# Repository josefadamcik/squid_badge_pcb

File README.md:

# squid_badge_pcb
SVG and KiCad files for a squid shaped pcb badge

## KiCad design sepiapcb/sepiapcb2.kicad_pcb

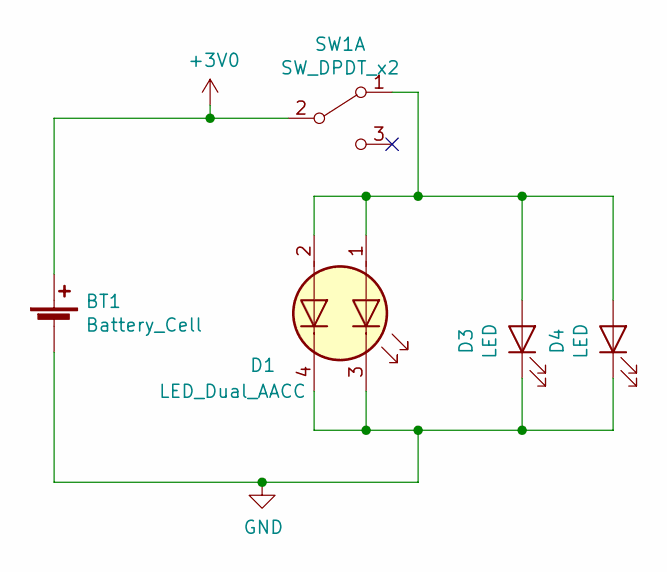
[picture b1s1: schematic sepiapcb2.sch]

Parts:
BT1: Battery_Cell; BatteryHolder_CR2032-BK-912xCR2032
D1: LED_Dual_AACC; sepia_footprint_enlarged_thttent_pcb
D3, D4: LED; LED_1206_3216Metric_ReverseMount_NoHole1.8x2.4mm
SW1: SW_DPDT_x2; SW_SPDT_PCM12

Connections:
+3V0: BT1.1 (+), SW1.2 (B)
GND: BT1.2 (-), D1.3 (K1), D1.4 (K2), D3.1 (K), D4.1 (K)
unnamed: D1.1 (A1), D1.2 (A2), D3.2 (A), D4.2 (A), SW1.1 (A)

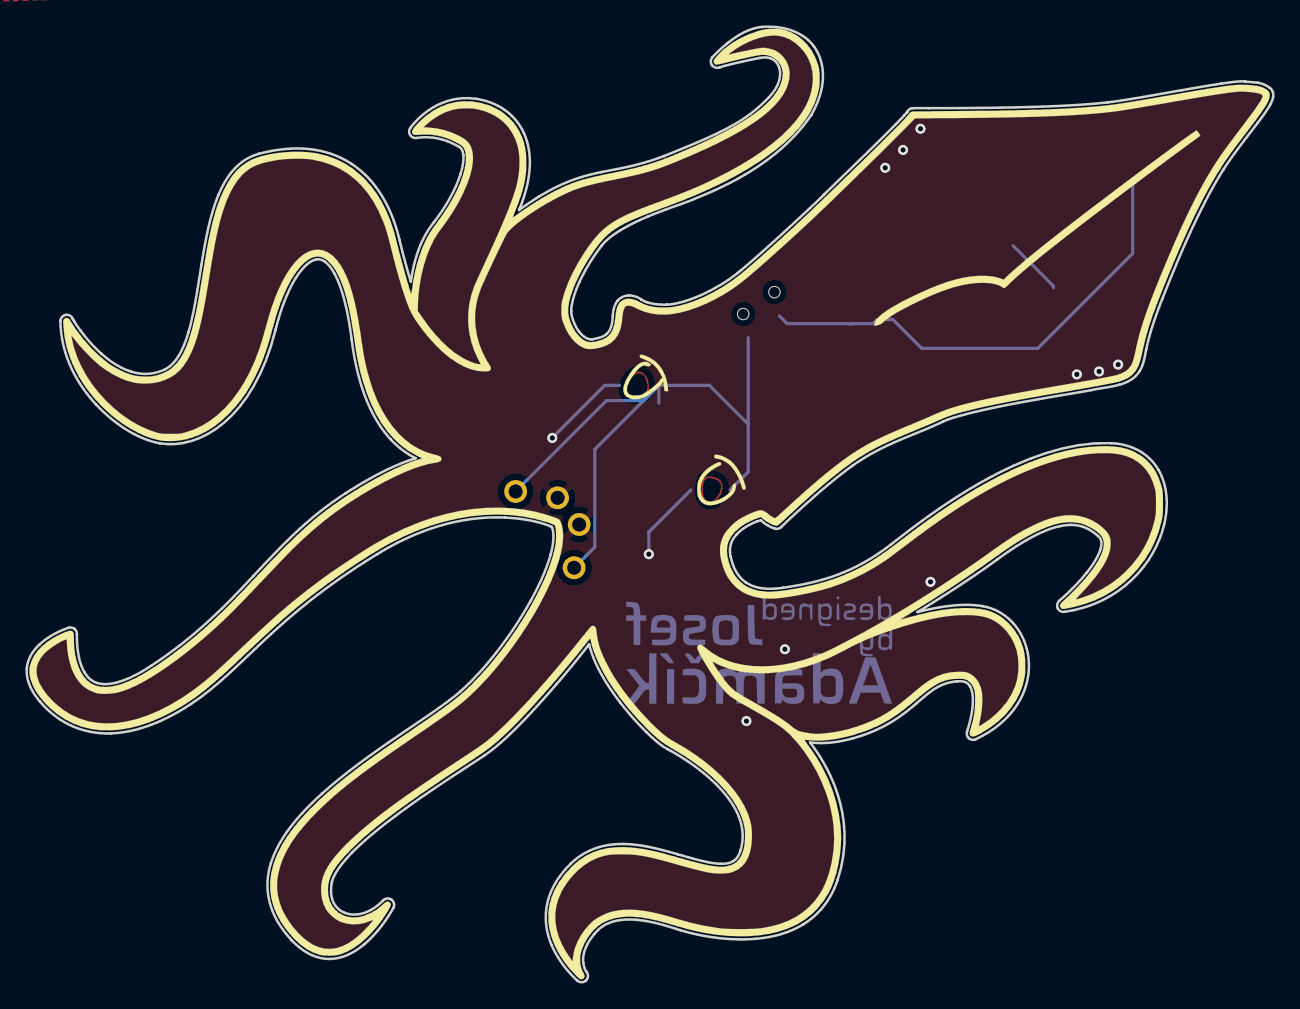
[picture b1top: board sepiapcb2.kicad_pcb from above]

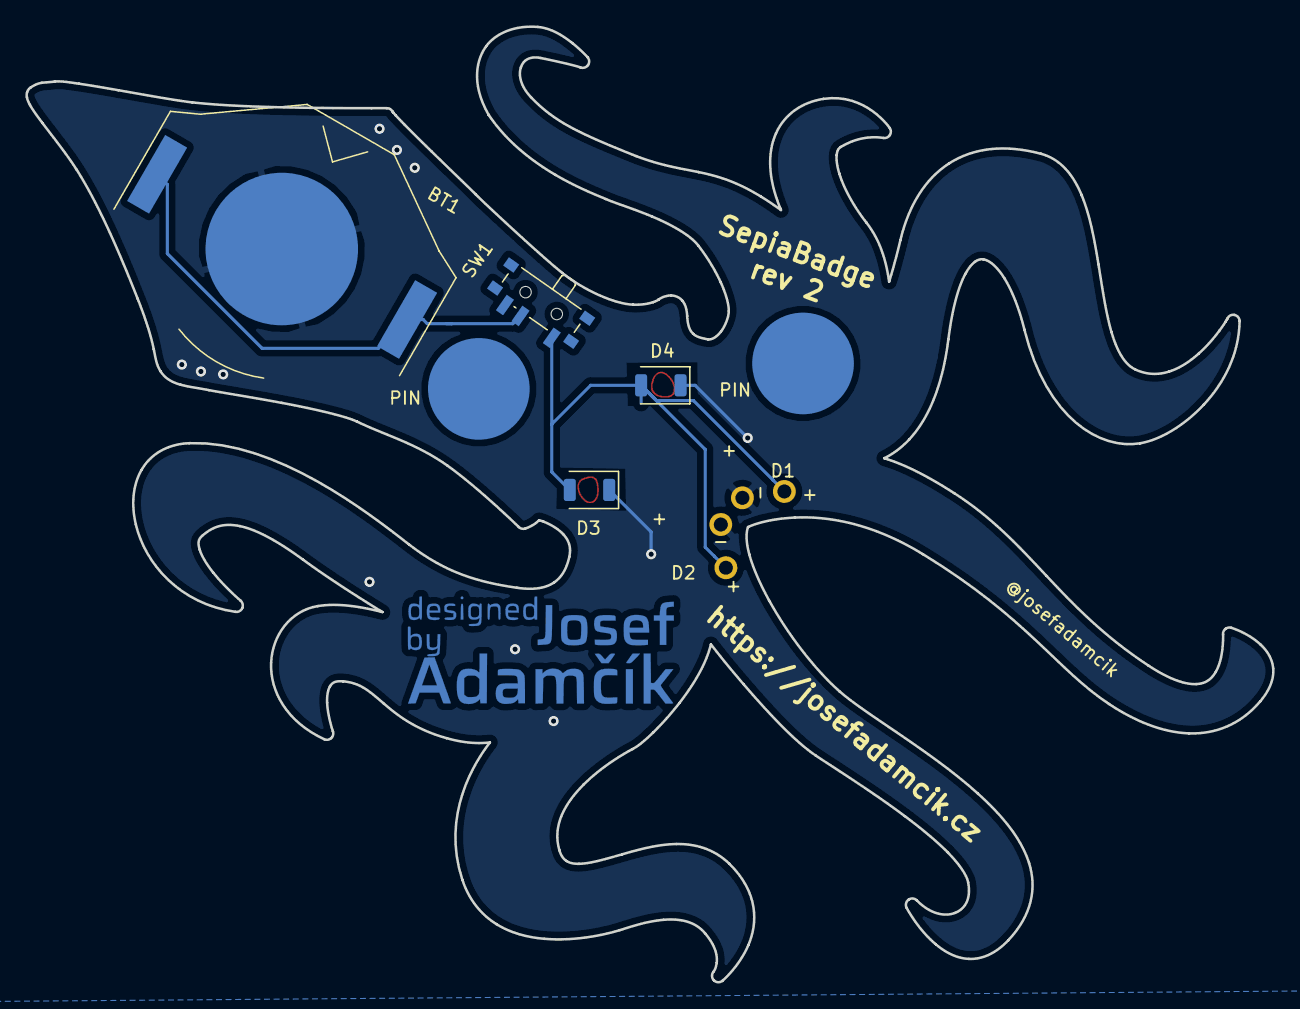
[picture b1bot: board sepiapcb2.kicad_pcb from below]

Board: 2 copper layers, 98.1 x 75.2 mm, 8 parts (7 on the bottom side), 3 nets.

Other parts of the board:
PIN: brooch_pin_pad
PIN#2: brooch_pin_pad
Ref**: Val**; josef_adamcik_20mm_cu_mask

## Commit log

2019-05-31 WIP converting scetch to vectors
2019-05-31 Sepia vectorised
2019-05-31 Removed clip path from main body
2019-05-31 WIP: main sepia body improvements
2019-06-10 it is blue
2019-06-11 New sepia footprint with pads for THT leds, zone fills for both sides
2019-06-12 TH coin cell battery holder
2019-06-12 WIP second, enlarged version
2019-06-12 Sepia footprint also enlarged
2019-06-12 Enlarged sepia almost done
2019-06-12 Added signature
2019-06-12 Fixe signature -> a curved one didn't work
2019-06-13 Adde pads for pins, gerebre files
2019-07-07 Clear and move files a bit. Add footprint library.
2019-07-07 Create LICENSE
2019-07-07 Update LICENSE
2019-07-20 Remove layer with bitmap from svg in order to make it smaller
2019-09-15 New battery holder footprint, logo, revision number.
2019-09-15 add new footprint with tht for tentacles
2019-09-15 PCB with THT tentacles
2019-09-15 Gerber fiele
